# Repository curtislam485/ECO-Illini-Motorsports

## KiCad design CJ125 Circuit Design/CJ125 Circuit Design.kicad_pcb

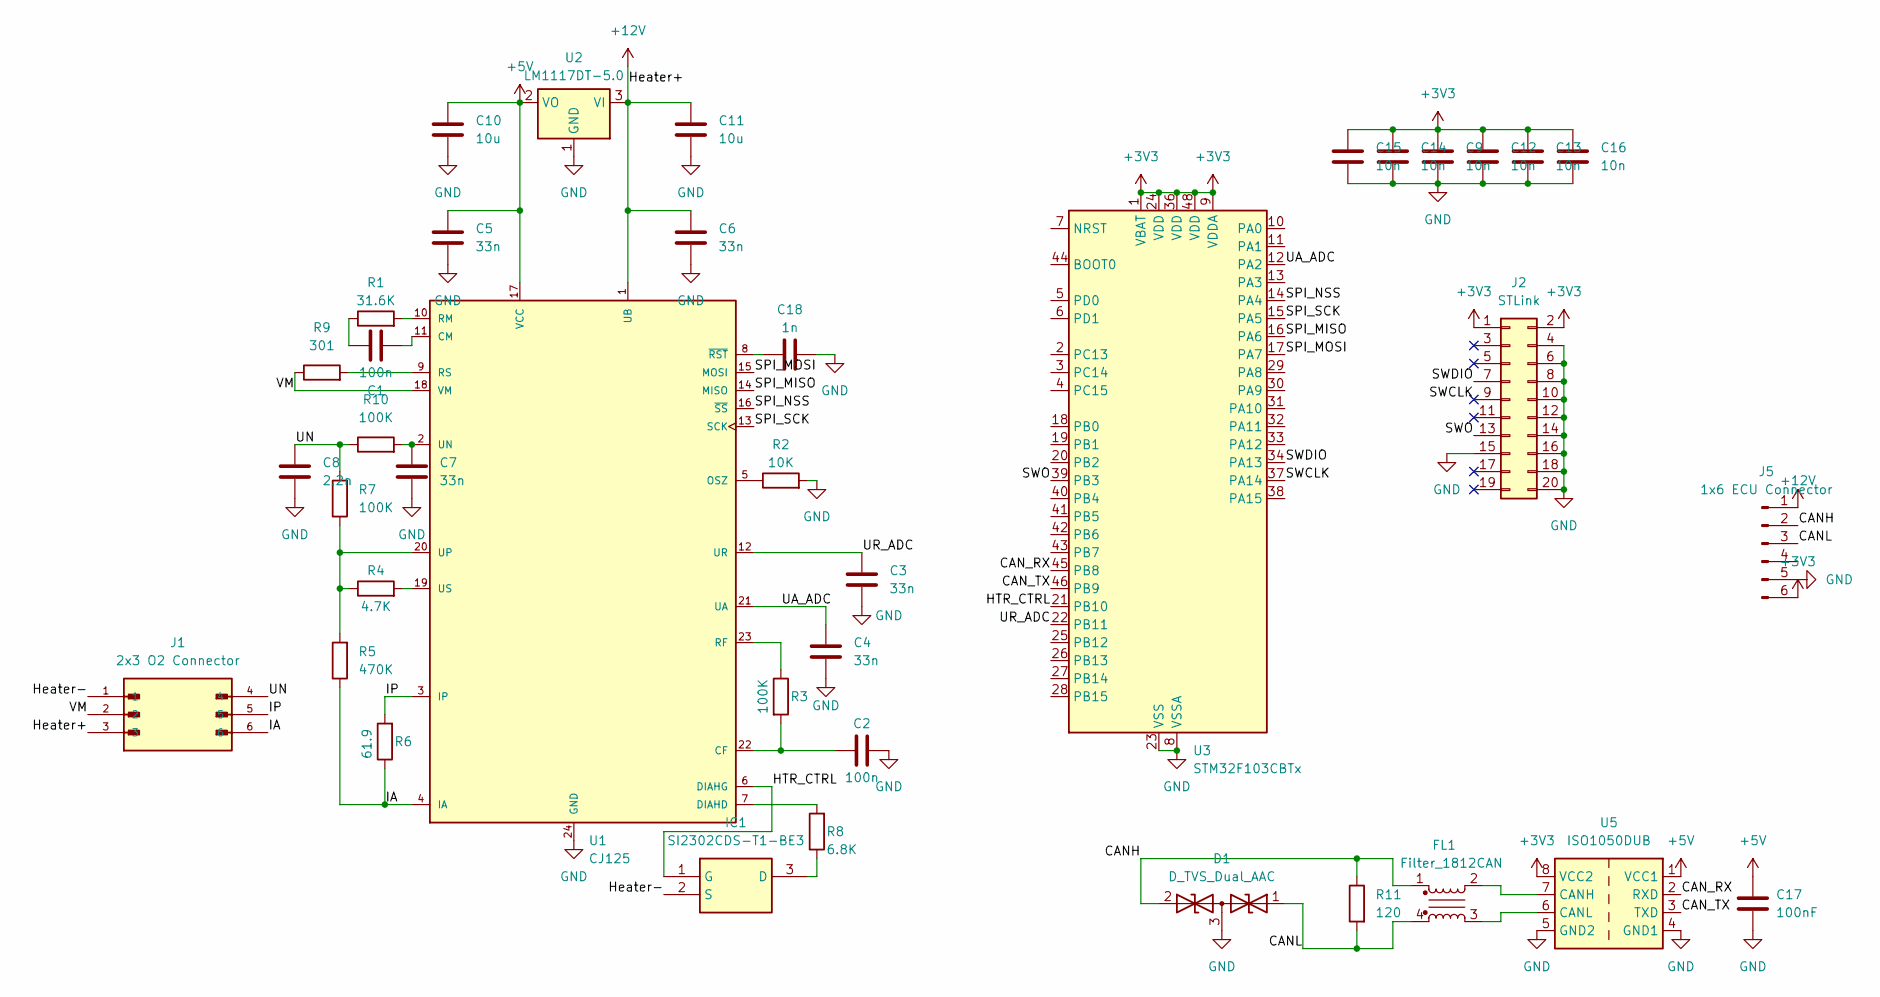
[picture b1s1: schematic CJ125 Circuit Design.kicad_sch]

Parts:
C1, C2: 100n; C_0603_1608Metric
C3, C4, C5, C6, C7: 33n; C_0603_1608Metric
C8: 2.2n; C_0603_1608Metric
C9, C12, C13, C14, C15, C16: 10n; C_0603_1608Metric
C10, C11: 10u; C_0603_1608Metric
C17: 100nF; C_0603_1608Metric
C18: 1n; C_0603_1608Metric
D1: D_TVS_Dual_AAC; SOT-23
FL1: Filter_1812CAN; L_CommonModeChoke_Coilcraft_1812CAN
IC1: SI2302CDS-T1-BE3; SOT95P237X112-3N; Mouser Part Number 78-SI2302CDS-T1-BE3
J1: 2x3 O2 Connector; MOLEX_1053101106; PARTREV H
J2: STLink; IDC-Header_2x10_P2.54mm_Vertical
J5: 1x6 ECU Connector; PinHeader_1x06_P1.00mm_Vertical
R1: 31.6K; R_0603_1608Metric
R2: 10K; R_0603_1608Metric
R3, R7, R10: 100K; R_0603_1608Metric
R4: 4.7K; R_0603_1608Metric
R5: 470K; R_0603_1608Metric
R6: 61.9; R_0603_1608Metric
R8: 6.8K; R_0603_1608Metric
R9: 301; R_0603_1608Metric
R11: 120; R_0603_1608Metric
U1: CJ125; SO24W
U2: LM1117DT-5.0; TO-252-3_TabPin2
U3: STM32F103CBTx; LQFP-48_7x7mm_P0.5mm
U5: ISO1050DUB; SOP-8_6.62x9.15mm_P2.54mm

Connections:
+3V3: C9.1, C12.1, C13.1, C14.1, C15.1, C16.1, J2.1, J2.2, J5.6, U3.1 (VBAT), U3.9 (VDDA), U3.24 (VDD), U3.36 (VDD), U3.48 (VDD), U5.8 (VCC2)
+5V: C5.1, C10.1, C17.1, U1.17 (VCC), U2.2 (VO), U5.1 (VCC1)
+12V: C6.1, C11.1, J1.3, J5.1, U1.1 (UB), U2.3 (VI)
/CANH: D1.2 (A2), FL1.1, J5.2, R11.1
/CANL: D1.1 (A1), FL1.4, J5.3, R11.2
/CAN_RX: U3.45 (PB8), U5.2 (RXD)
/CAN_TX: U3.46 (PB9), U5.3 (TXD)
/HTR_CTRL: IC1.1 (G), U1.6 (DIAHG), U3.21 (PB10)
/Heater-: IC1.2 (S), J1.1
/IA: J1.6, R5.1, R6.1, U1.4 (IA)
/IP: J1.5, R6.2, U1.3 (IP)
/SPI_MISO: U1.14 (MISO), U3.16 (PA6)
/SPI_MOSI: U1.15 (MOSI), U3.17 (PA7)
/SPI_NSS: U1.16 (~SS), U3.14 (PA4)
/SPI_SCK: U1.13 (SCK), U3.15 (PA5)
/SWCLK: J2.9, U3.37 (PA14)
/SWDIO: J2.7, U3.34 (PA13)
/SWO: J2.13, U3.39 (PB3)
/UA_ADC: C4.1, U1.21 (UA), U3.12 (PA2)
/UN: C8.2, J1.4, R7.2, R10.1
/UR_ADC: C3.1, U1.12 (UR), U3.22 (PB11)
/VM: J1.2, R9.1, U1.18 (VM)
GND: C2.2, C3.2, C4.2, C5.2, C6.2, C7.1, C8.1, C9.2, C10.2, C11.2, C12.2, C13.2, C14.2, C15.2, C16.2, C17.2, C18.2, D1.3 (common), J2.4, J2.6, J2.8, J2.10, J2.12, J2.14, J2.15, J2.16, J2.18, J2.20, J5.5, R2.2, U1.24 (GND), U2.1 (GND), U3.8 (VSSA), U3.23 (VSS), U3.35 (VSS), U3.47 (VSS), U5.4 (GND1), U5.5 (GND2)
unnamed: C1.1, R1.1
unnamed: IC1.3 (D), R8.1
unnamed: C2.1, R3.2, U1.22 (CF)
unnamed: C1.2, U1.11 (CM)
unnamed: R8.2, U1.7 (DIAHD)
unnamed: R2.1, U1.5 (OSZ)
unnamed: R3.1, U1.23 (RF)
unnamed: R1.2, U1.10 (RM)
unnamed: R9.2, U1.9 (RS)
unnamed: C7.2, R10.2, U1.2 (UN)
unnamed: R4.1, R5.2, R7.1, U1.20 (UP)
unnamed: R4.2, U1.19 (US)
unnamed: C18.1, U1.8 (~RST)
unnamed: FL1.2, U5.7 (CANH)
unnamed: FL1.3, U5.6 (CANL)

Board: 2 copper layers, 39 parts (0 on the bottom side), 38 nets, no tracks yet.

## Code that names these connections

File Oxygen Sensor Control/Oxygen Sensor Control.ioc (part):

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Mcu.Name=STM32F103C(8-B)Tx
Mcu.Package=LQFP48
Mcu.UserName=STM32F103C8Tx
PA1.Signal=ADCx_IN1
PA13.Signal=SYS_JTMS-SWDIO
PA14.Signal=SYS_JTCK-SWCLK
PA2.GPIOParameters=GPIO_Label
PA2.GPIO_Label=UA_ADC
PA2.Signal=ADCx_IN2
PA4.Mode=NSS_Signal_Hard_Output
PA4.Signal=SPI1_NSS
PA5.Mode=Full_Duplex_Master
PA5.Signal=SPI1_SCK
PA6.Mode=Full_Duplex_Master
PA6.Signal=SPI1_MISO
PA7.Mode=Full_Duplex_Master
PA7.Signal=SPI1_MOSI
PB10.GPIOParameters=GPIO_Label
PB10.GPIO_Label=HTR_CTRL
PB10.Signal=GPIO_Output
PB11.GPIOParameters=GPIO_Label
PB11.GPIO_Label=UR_ADC
PB11.Signal=GPXTI11
PB3.Signal=SYS_JTDO-TRACESWO
PB8.Mode=CAN_Activate
PB8.Signal=CAN_RX
PB9.Mode=CAN_Activate
PB9.Signal=CAN_TX
board=custom

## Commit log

2023-10-02 add cj125 folder
2023-10-02 added rest of file
2023-10-02 cj125 code
2023-10-02 cj125
2023-10-04 add c file
2023-10-06 cj125 code modifications + hspi INIT
2023-10-13 more adc/dac stuf
2023-10-16 idk wut i coded tbh
2023-11-17 updated a bunch of cj125 stuff
2023-12-04 added a bunch of stuff for hte board
2023-12-16 worked on some software but mainly just o2 board design
2024-01-03 new board design
